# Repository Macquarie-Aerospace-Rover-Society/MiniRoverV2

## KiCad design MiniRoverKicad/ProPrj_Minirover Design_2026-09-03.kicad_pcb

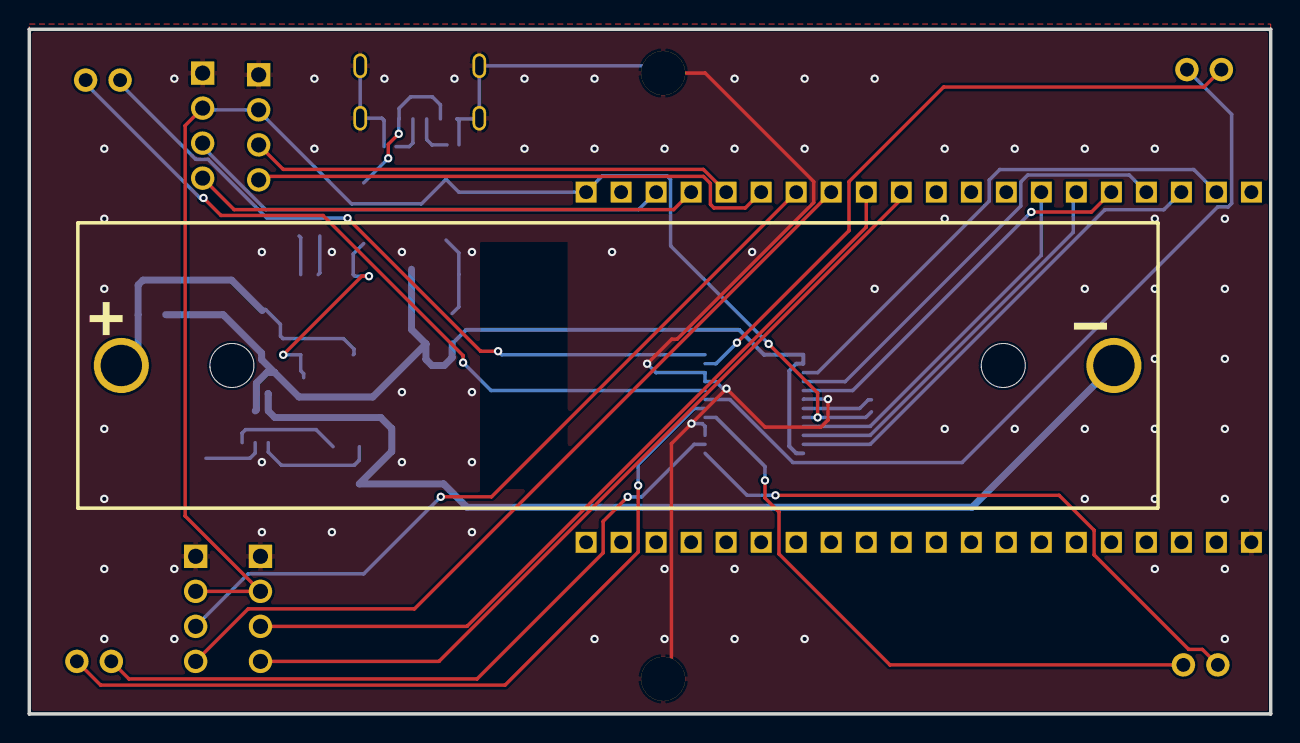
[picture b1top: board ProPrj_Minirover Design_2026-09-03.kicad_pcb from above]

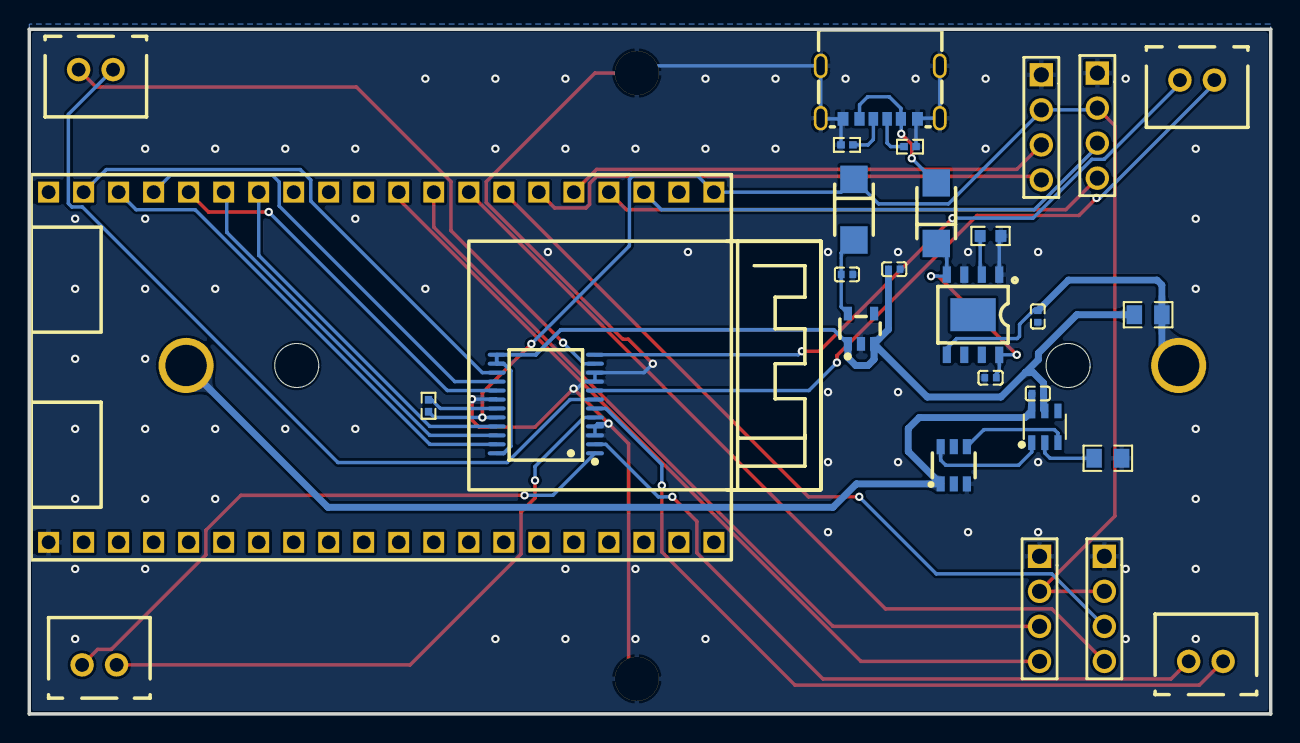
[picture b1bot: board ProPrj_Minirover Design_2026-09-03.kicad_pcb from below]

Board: 2 copper layers, 90.0 x 49.7 mm, 29 parts (28 on the bottom side), 37 nets.

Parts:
B1: BAT-TH_BH-18650-A1BJ033
C4, C5, C6, C7, C8: C0402
D1, D2: SMF_L3.5-W2.5-LS4.5-RD
EX1, EX2, EX3, EX4: HDR-TH_4P-P2.54-V-M-1
Motor1, Motor2, Motor3, Motor4: CONN-TH_B2B-XH-A-LF-SN
Q1: SOT-23-6_L2.9-W1.6-P0.95-LS2.8-BR
R1, R3, R6: R0402
R2: R0603
R4, R5: R0805
U1: SSOP-24_L8.3-W5.6-P0.65-LS7.6-BL
U2: ESP32-S3-CAM KP
U3: SOT-23-6_L2.9-W1.6-P0.95-LS2.9-BL
U5: ESOP-8_L4.9-W3.9-P1.27-LS6.0-BL-EP
U6: SOT-23-5_L2.9-W1.6-P0.95-LS2.8-BR
USB1: USB-C-SMD_TYPE-C-6P

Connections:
1EXP1: EX1.3, U2.9
1EXP2: EX1.4, U2.10
2EXP1: EX2.3, U2.7
2EXP2: EX2.4, U2.8
3EXP1: EX3.3, U2.5
3EXP2: EX3.4, U2.6
4EXP1: EX4.3, U2.3
4EXP2: EX4.4, U2.4
$B1_1: B1.1, C6.1, R4.2, U5.5
$C5_1: C5.1, D2.1, U5.4, U5.8
$C8_2: C8.2, D1.2, U6.5
$D2_2: D2.2, USB1.A9, USB1.B9
$Motor1_1: Motor1.1, U1.12
$Motor1_2: Motor1.2, U1.8
$Motor2_1: Motor2.1, U1.11
$Motor2_2: Motor2.2, U1.7
$Motor3_1: Motor3.1, U1.6
$Motor3_2: Motor3.2, U1.2
$Motor4_1: Motor4.1, U1.5
$Motor4_2: Motor4.2, U1.1
$R1_1: R1.1, U1.19
$R2_1: R2.1, U5.2
$R3_2: R3.2, USB1.B5
$R6_2: R6.2, USB1.A5
AIN1: U1.21, U2.14
AIN2: U1.22, U2.15
BGND: B1.2, C4.1, Q1.1, U3.6
BIN1: U1.17, U2.16
BIN2: U1.16, U2.17
C Gate: Q1.4, U3.3
D Gate: Q1.6, U3.1
GND: C5.2, C6.2, C7.1, C8.1, EX1.1, EX2.1, EX3.1, EX4.1, Q1.3, R2.2, R3.1, R5.1, R6.1, U1.3, U1.4, U1.9, U1.10, U1.18, U2.21, U5.1, U5.3, U6.2, USB1.1, USB1.2, USB1.A12, USB1.B12
PWMA: U1.23, U2.18
PWMB: U1.15, U2.19
Sense: R5.2, U3.2
VBAT: C4.2, C7.2, R4.1, U1.13, U1.14, U1.24, U3.5, U6.1, U6.3
VCC: D1.1, EX1.2, EX2.2, EX3.2, EX4.2, R1.2, U1.20, U2.1
